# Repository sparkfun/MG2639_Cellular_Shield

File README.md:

**Note:Retired Product**
This product has been retired from our catalog and is no longer for sale. This page is made available for those looking for datasheets and the simply curious.

SparkFun MG2639 Cellular Shield
=========================

[*SparkFun MG2639 Cellular Shield (CEL-13120)*](https://www.sparkfun.com/products/13120)

The SparkFun MG2639 Cellular shield is an Arduino compatible shield that gives the user access to the MG2639_V3 GSM+GPS module. The module is capable of accquiring a GPS location as well as communication with GSM networks all over the world. Phonecalls can be made, texts sent, and data pushed to and read from web pages. All the supporting circuitry is provided including translation from 2.8V of the module to a user selectable 3.3V or 5V.

The main interface is two software serial ports.

Power can be provided either from the Arduino board's VIN or from an external battery such as a lithium polymer.

Repository Contents
-------------------

* **/Firmware** - Example sketches that work without the Arduino library.
* **/Hardware** - Schematic and PCB layout for the shield. Also includes an eagle library containing the various custom footprints for this shield. Specifically the MG2639 footprint.
* **/Documentation** - The AT command set, hardware guide, and various other datasheets.
* **/Libraries** - The SparkFun MG2639 Cellular Shield library.
* **/Production** - Production panel files.
* **[Hookup Guide](https://learn.sparkfun.com/tutorials/retired---mg2639-cellular-shield-hookup-guide)** - To get started using the MG2639 Cellular Shield, check out our tutorial!

License Information
-------------------
The hardware is released under [CERN Open Hardware License 1.2](http://www.ohwr.org/attachments/2388/cern_ohl_v_1_2.txt).
The code is beerware; if you see me (or any other SparkFun employee) at the local, and you've found our code helpful, please buy us a round!

Distributed as-is; no warranty is given.

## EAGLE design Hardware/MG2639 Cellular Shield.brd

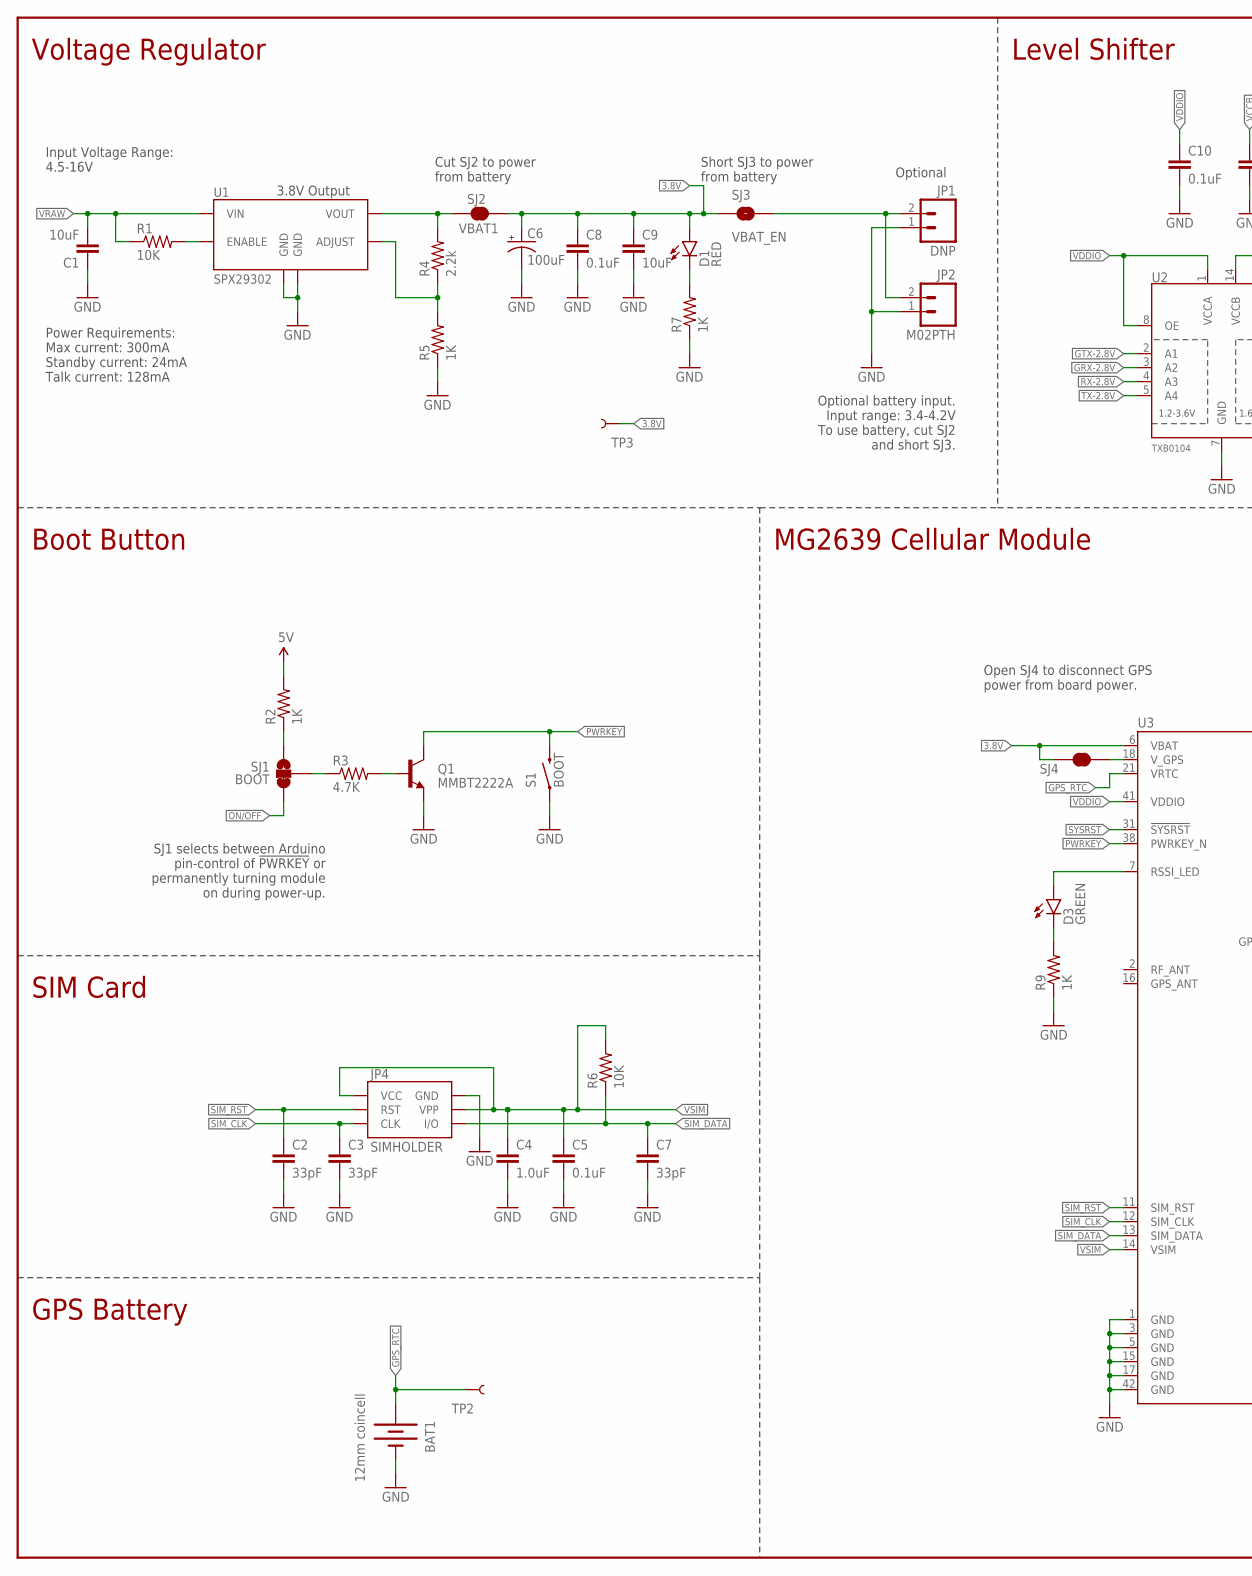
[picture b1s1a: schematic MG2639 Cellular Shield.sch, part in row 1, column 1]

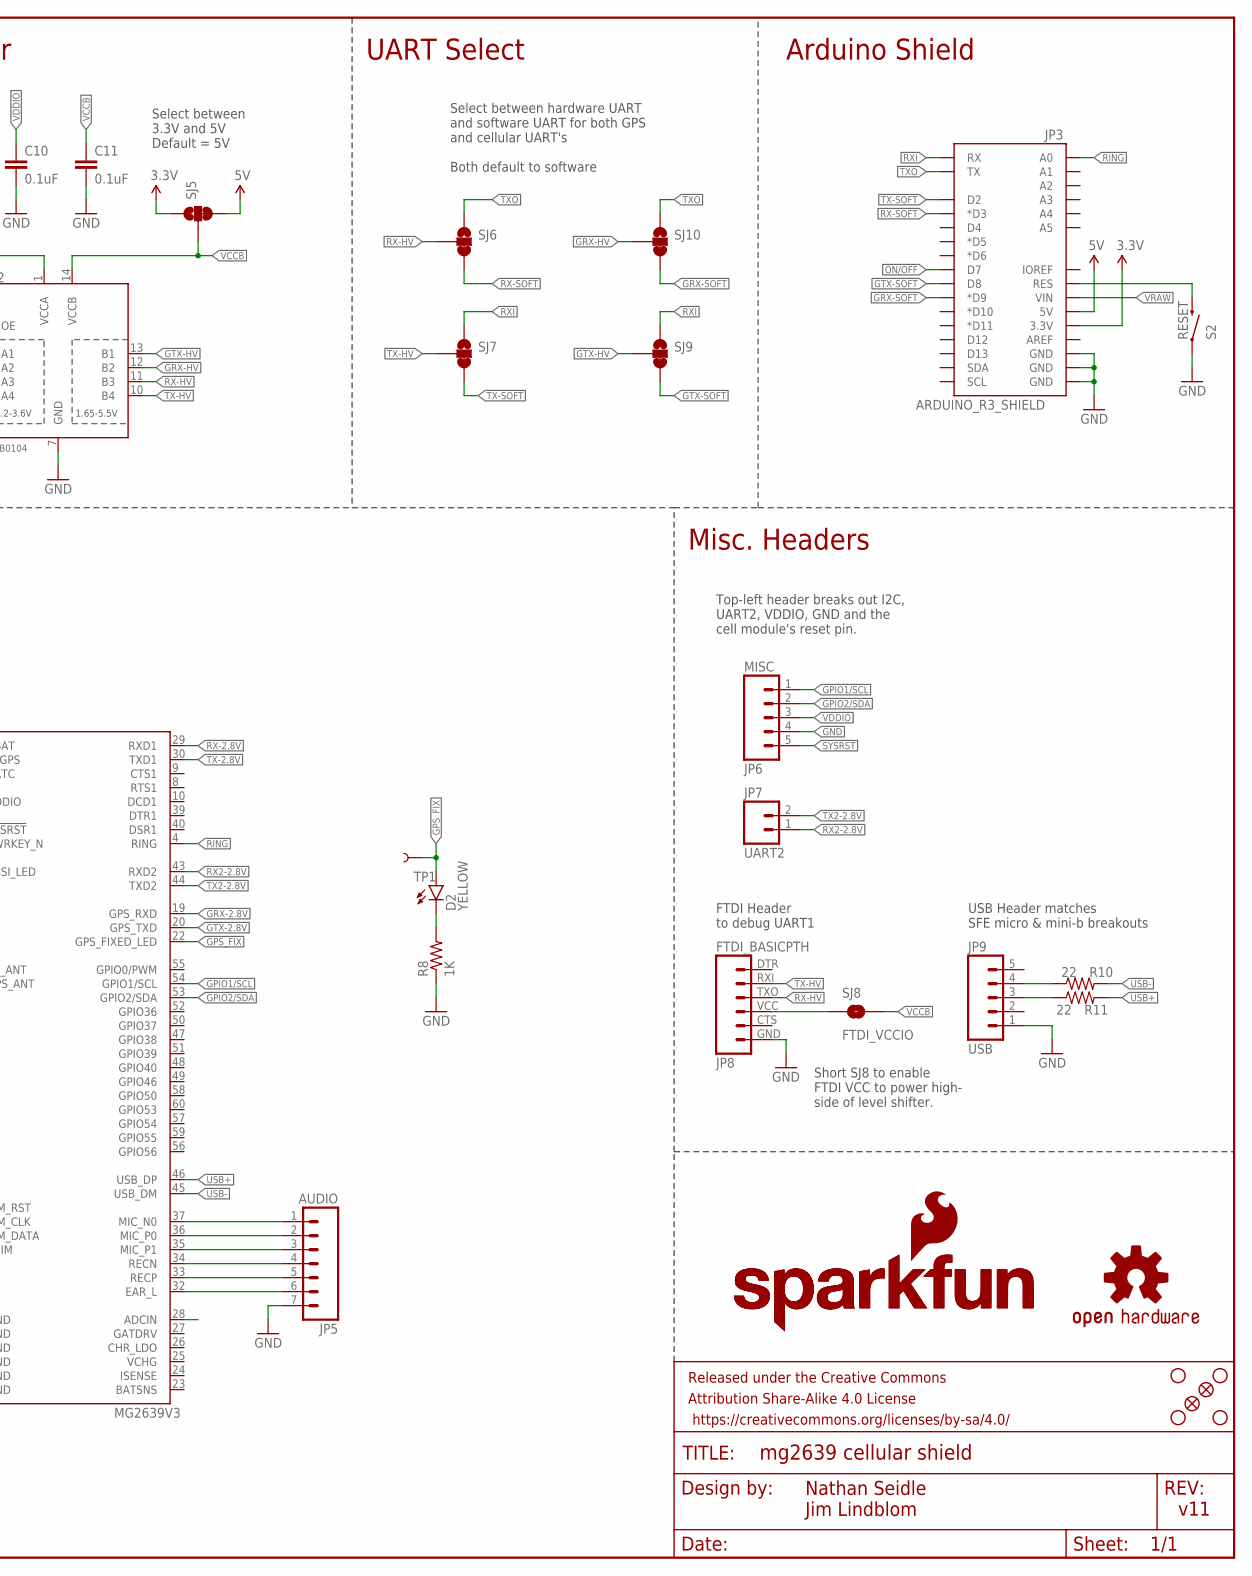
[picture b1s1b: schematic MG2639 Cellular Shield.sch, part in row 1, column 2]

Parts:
BAT1: 12mm coincell; BATTCON_12MM
C1, C9: 10uF; 1210
C2, C3, C7: 33pF; 0603-CAP
C4: 1.0uF; 0603-CAP
C5, C8, C10, C11: 0.1uF; 0603-CAP
C6: 100uF; EIA7343
D1: RED; LED-1206
D2: YELLOW; LED-1206
D3: GREEN; LED-1206
FID1, FID2: FIDUCIAL1X2; FIDUCIAL-1X2
FRAME1: FRAME-LEDGER; CREATIVE_COMMONS
JP1: DNP; JST-2-PTH
JP2: M02PTH; 1X02
JP3: ARDUINO_R3_SHIELD; UNO_R3_SHIELD_NOLABELS
JP4: SIMHOLDER
JP5: AUDIO; 1X07
JP6: MISC; 1X05
JP7: UART2; 1X02
JP8: FTDI_BASICPTH; FTDI_BASIC
JP9: USB; 1X05
LOGO1: SFE_LOGO_NAME.1_INCH; SFE_LOGO_NAME_.1
LOGO2: SFE_LOGO_NAME_FLAME.2_INCH; SFE_LOGO_NAME_FLAME_.2
LOGO3: OSHW-LOGOS; OSHW-LOGO-S
Q1: MMBT2222A; SOT23-3
R1, R6: 10K; 0603-RES
R2, R5, R7, R8, R9: 1K; 0603-RES
R3: 4.7K; 0603
R4: 2.2k; 0603-RES
R10, R11: 22; 0603-RES
S1: BOOT; TACTILE-SWITCH-SMD
S2: RESET; TACTILE-SWITCH-SMD
SJ1: BOOT; PAD-JUMPER-3-2OF3_NC_BY_TRACE_YES_SILK_FULL_BOX
SJ2: VBAT1; PAD-JUMPER-2-NC_BY_TRACE_YES_SILK
SJ3: VBAT_EN; PAD-JUMPER-2-NO_YES_SILK
SJ4: JUMPER-PAD-2-NC_BY_TRACE; PAD-JUMPER-2-NC_BY_TRACE_YES_SILK
SJ5, SJ6, SJ7, SJ9, SJ10: JUMPER-PAD-3-2OF3_NC_BY_TRACE; PAD-JUMPER-3-2OF3_NC_BY_TRACE_YES_SILK_FULL_BOX
SJ8: FTDI_VCCIO; PAD-JUMPER-2-NO_YES_SILK
STANDOFF1, STANDOFF2, STANDOFF3, STANDOFF4: STAND-OFF
TP1, TP2, TP3: TEST-POINT3X5; PAD.03X.05
U1: SPX29302; Q5-DD_SPX29300
U2: TXB0104; SO14
U3: MG2639V3; MG2639

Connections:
3.3V: JP3.3.3V, SJ5.1
3.8V: C6.A (+), C8.1, C9.1, D1.A, SJ2.2, SJ3.1, SJ4.1, TP3.P$1, U3.6 (VBAT)
5V: JP3.5V, R2.2, SJ5.3
!PWRKEY: Q1.3 (C), S1.3 (2), U3.38 (PWRKEY_N)
!SYSRST: JP6.5, U3.31 (!SYSRST)
ADCIN: U3.28 (ADCIN)
ADJUST: R4.1, R5.2, U1.5 (ADJUST)
EAR_L: JP5.6, U3.32 (EAR_L)
GND: BAT1.GND (-), C1.1, C2.2, C3.2, C4.2, C5.2, C6.C (-), C7.2, C8.2, C9.2, C10.2, C11.2, JP1.1, JP2.1, JP3.GND@0 (GND), JP3.GND@1 (GND), JP3.GND@2 (GND), JP4.C5 (GND), JP5.7, JP6.4, JP8.GND (6), JP9.1, Q1.2 (E), R5.1, R7.1, R8.1, R9.1, S1.1, S2.1, U1.3 (GND), U1.6 (GND), U2.7 (GND), U3.1 (GND), U3.3 (GND), U3.5 (GND), U3.15 (GND), U3.17 (GND), U3.42 (GND)
GPIO1/SCL: JP6.1, U3.54 (GPIO1/SCL)
GPIO2/SDA: JP6.2, U3.53 (GPIO2/SDA)
GPS_FIX: D2.A, TP1.P$1, U3.22 (GPS_FIXED_LED)
GPS_RTC: BAT1.PWR@1 (+), TP2.P$1, U3.21 (VRTC)
GRX-2.8V: U2.3 (A2), U3.19 (GPS_RXD)
GRX-HV: SJ10.2, U2.12 (B2)
GRX-SOFT: JP3.D9 (*D9), SJ10.3
GTX-2.8V: U2.2 (A1), U3.20 (GPS_TXD)
GTX-HV: SJ9.2, U2.13 (B1)
GTX-SOFT: JP3.D8, SJ9.3
MIC_N0: JP5.1, U3.37 (MIC_N0)
MIC_P0: JP5.2, U3.36 (MIC_P0)
MIC_P1: JP5.3, U3.35 (MIC_P1)
unnamed: R1.2, U1.1 (ENABLE)
unnamed: JP9.4, R10.1
unnamed: Q1.1 (B), R3.2
unnamed: R4.2, SJ2.1, U1.4 (VOUT)
unnamed: R3.1, SJ1.2
unnamed: R2.1, SJ1.1
unnamed: D3.A, U3.7 (RSSI_LED)
unnamed: D3.C, R9.2
unnamed: D2.C, R8.2
unnamed: JP9.3, R11.1
unnamed: JP8.VCC (4), SJ8.1
unnamed: JP1.2, JP2.2, SJ3.2
unnamed: D1.C, R7.2
ON/OFF: JP3.D7, SJ1.3
RECN: JP5.4, U3.34 (RECN)
RECP: JP5.5, U3.33 (RECP)
RESET: JP3.RES, S2.3 (2)
RING: JP3.A0, U3.4 (RING)
RX2-2.8V: JP7.1, U3.43 (RXD2)
RX-2.8V: U2.4 (A3), U3.29 (RXD1)
RX-HV: JP8.TXO (3), SJ6.2, U2.11 (B3)
RX-SOFT: JP3.D3 (*D3), SJ6.3
RXI: JP3.RX, SJ7.1, SJ9.1
SIM_CLK: C3.1, JP4.C3 (CLK), U3.12 (SIM_CLK)
SIM_DATA: C7.1, JP4.C7 (I/O), R6.1, U3.13 (SIM_DATA)
SIM_RST: C2.1, JP4.C2 (RST), U3.11 (SIM_RST)
TX2-2.8V: JP7.2, U3.44 (TXD2)
TX-2.8V: U2.5 (A4), U3.30 (TXD1)
TX-HV: JP8.RXI (2), SJ7.2, U2.10 (B4)
TX-SOFT: JP3.D2, SJ7.3
TXO: JP3.TX, SJ6.1, SJ10.1
USB+: R11.2, U3.46 (USB_DP)
USB-: R10.2, U3.45 (USB_DM)
VCCB: C11.1, SJ5.2, SJ8.2, U2.14 (VCCB)
VCHG: U3.25 (VCHG)
VDDIO: C10.1, JP6.3, U2.1 (VCCA), U2.8 (OE), U3.41 (VDDIO)
VRAW: C1.2, JP3.VIN, R1.1, U1.2 (VIN)
VSIM: C4.1, C5.1, JP4.C1 (VCC), JP4.C6 (VPP), R6.2, U3.14 (VSIM)
V_GPS: SJ4.2, U3.18 (V_GPS)

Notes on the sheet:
3.8V Output
Select between 3.3V and 5V Default = 5V
Select between hardware UART and software UART for both GPS and cellular UART's Both default to software
Cut SJ2 to power from battery
Optional
Nathan Seidle Jim Lindblom
Open SJ4 to disconnect GPS power from board power.
v11
Voltage Regulator
Level Shifter
UART Select
Arduino Shield
Misc. Headers
MG2639 Cellular Module
Boot Button
SIM Card
GPS Battery
FTDI Header to debug UART1
USB Header matches SFE micro & mini-b breakouts
Top-left header breaks out I2C, UART2, VDDIO, GND and the cell module's reset pin.
Short SJ3 to power from battery
Optional battery input. Input range: 3.4-4.2V To use battery, cut SJ2 and short SJ3.
Input Voltage Range: 4.5-16V
Power Requirements: Max current: 300mA Standby current: 24mA Talk current: 128mA
Short SJ8 to enable FTDI VCC to power high- side of level shifter.
SJ1 selects between Arduino pin-control of !PWRKEY! or permanently turning module on during power-up.

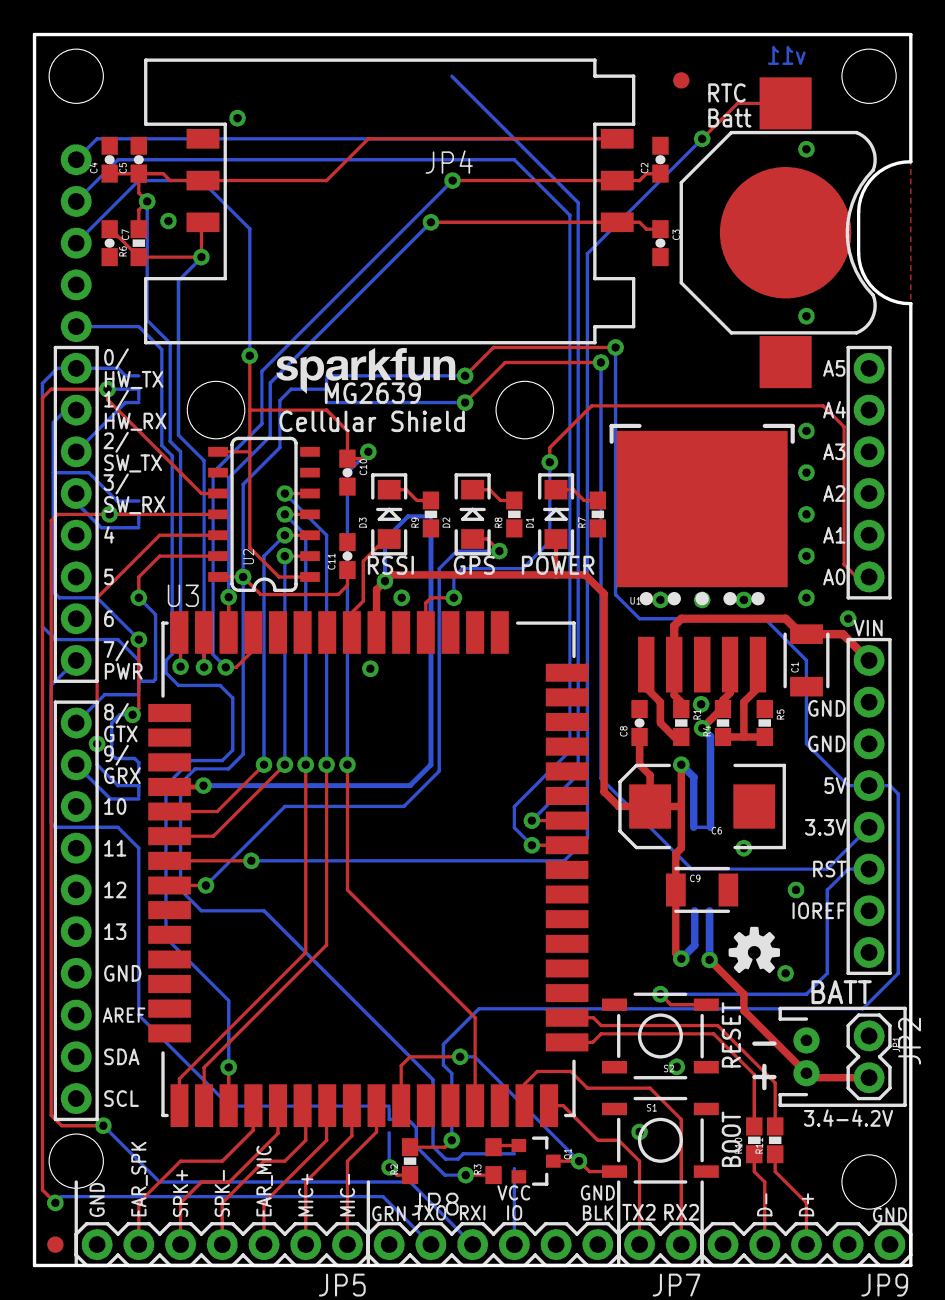
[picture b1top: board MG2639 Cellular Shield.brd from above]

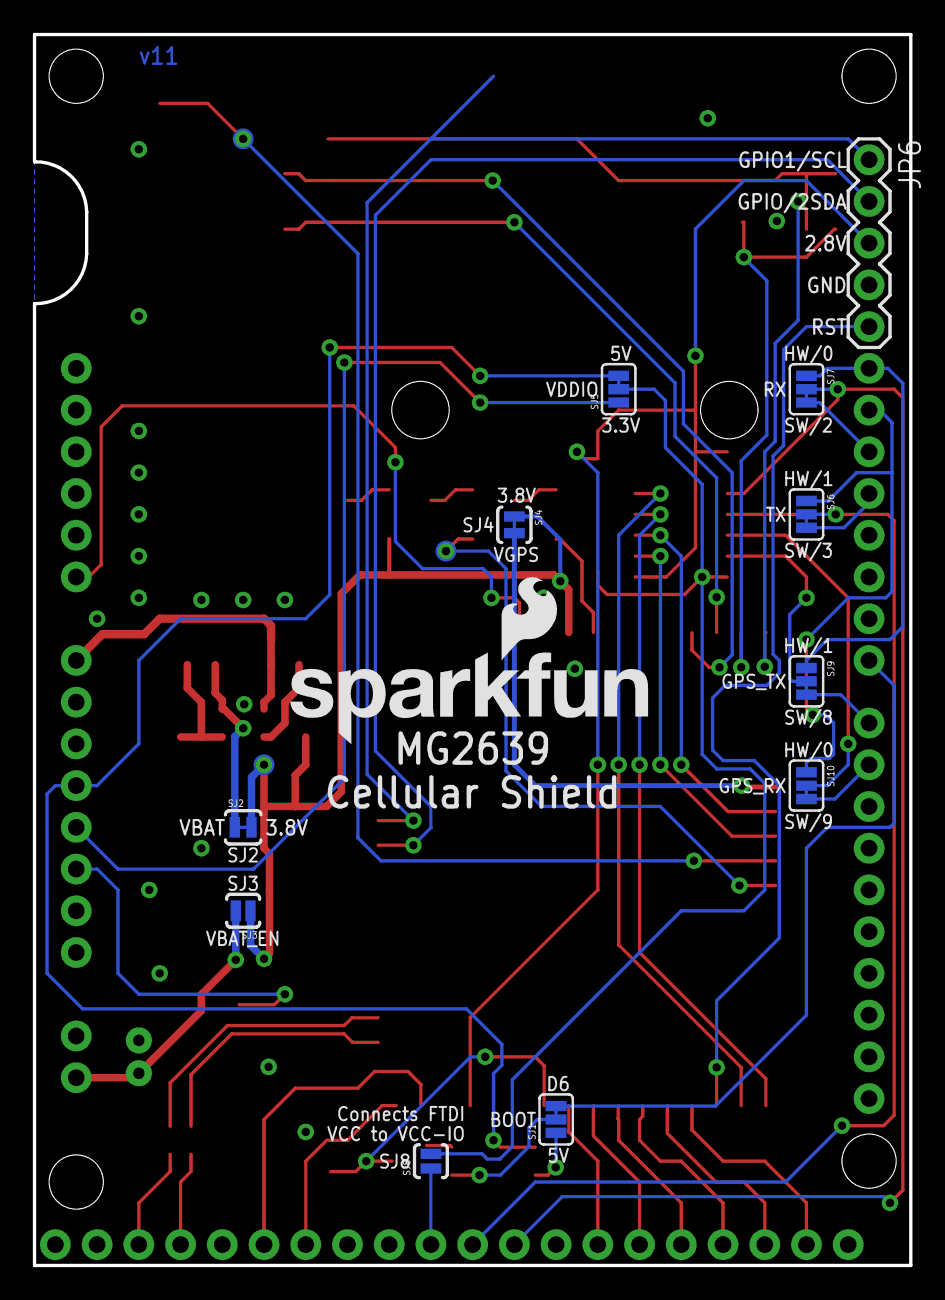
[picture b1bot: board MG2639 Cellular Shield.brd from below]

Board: 2 copper layers, 53.3 x 74.9 mm, 64 parts (15 on the bottom side), 59 nets.

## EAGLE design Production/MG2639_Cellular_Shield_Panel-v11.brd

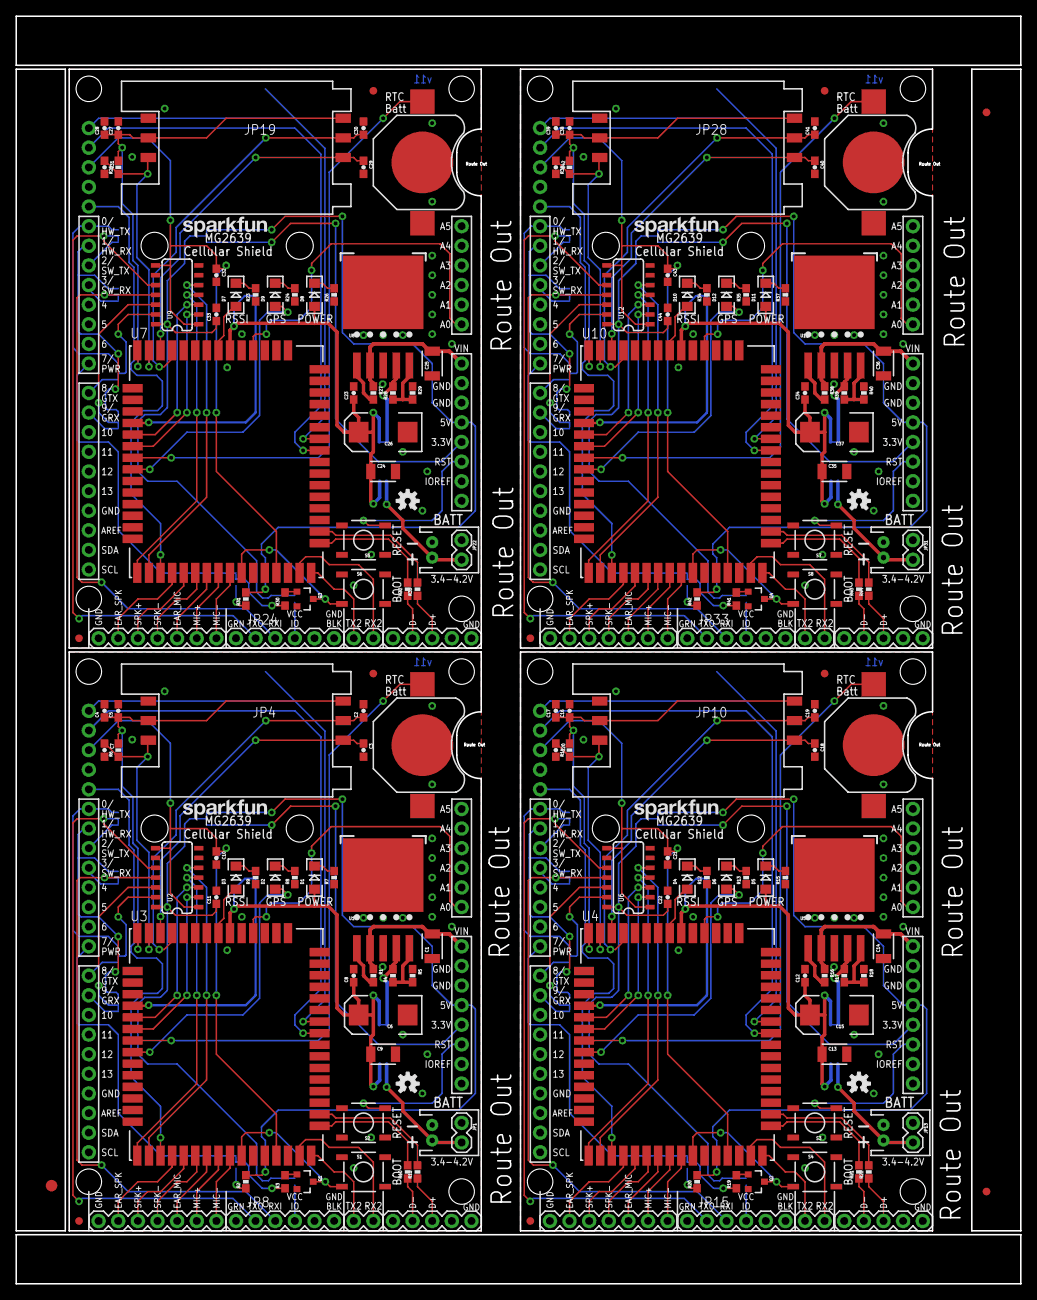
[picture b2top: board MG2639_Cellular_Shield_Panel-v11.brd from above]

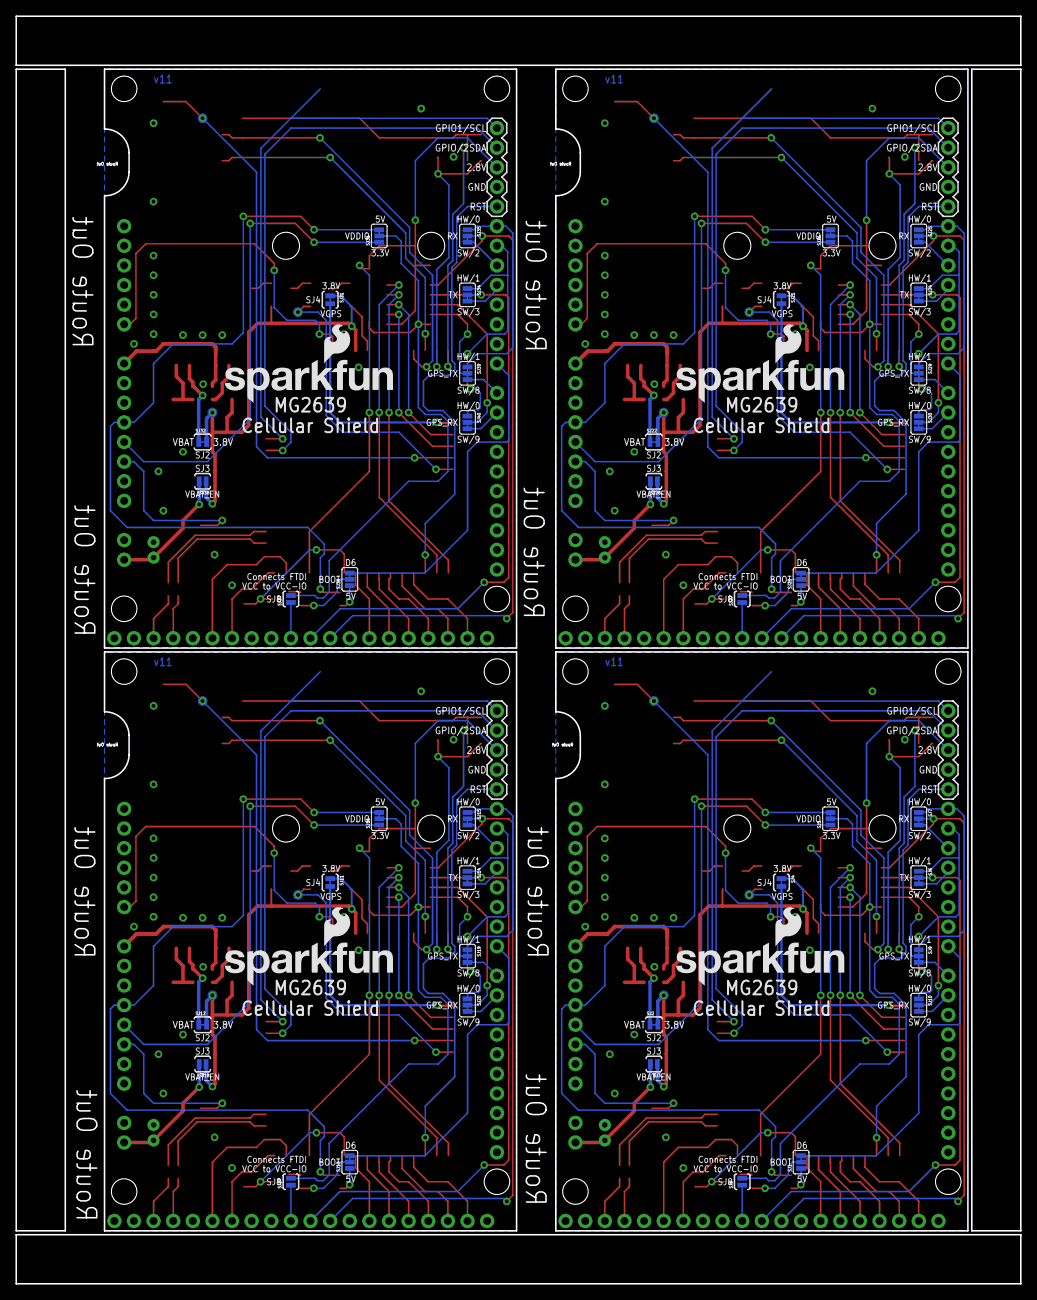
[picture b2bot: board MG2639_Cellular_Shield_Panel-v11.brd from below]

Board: 2 copper layers, 130.0 x 164.1 mm, 255 parts (60 on the bottom side), 236 nets.

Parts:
BAT1, BAT2, BAT3, BAT4: 12mm coincell; BATTCON_12MM
C1, C9, C13, C14, C24, C25, C35, C36: 10uF; 1210
C2, C3, C7, C18, C19, C20, C29, C30, C31, C40, C41, C42: 33pF; 0603-CAP
C4, C17, C28, C39: 1.0uF; 0603-CAP
C5, C8, C10, C11, C12, C16, C21, C22, C23, C27, C32, C33, C34, C38, C43, C44: 0.1uF; 0603-CAP
C6, C15, C26, C37: 100uF; EIA7343
D1, D5, D8, D11: RED; LED-1206
D2, D6, D9, D12: YELLOW; LED-1206
D3, D4, D7, D10: GREEN; LED-1206
E$1: FIDUCIAL-1.5X3
E$4, E$5: FIDUCIAL-1X2
FID1, FID2, FID3, FID4, FID5, FID6, FID7, FID8: FIDUCIAL1X2; FIDUCIAL-1X2
JP1, JP13, JP22, JP31: LiPo; JST-2-PTH
JP2, JP16, JP25, JP34: M02PTH; 1X02
JP3, JP11, JP20, JP29: ARDUINO_R3_SHIELD; UNO_R3_SHIELD_NOLABELS
JP4, JP10, JP19, JP28: SIMHOLDER
JP5, JP12, JP21, JP30: AUDIO; 1X07
JP6, JP18, JP27, JP36: MISC; 1X05
JP7, JP17, JP26, JP35: UART2; 1X02
JP8, JP15, JP24, JP33: FTDI_BASICPTH; FTDI_BASIC
JP9, JP14, JP23, JP32: USB; 1X05
LOGO1, LOGO6, LOGO9, LOGO12: SFE_LOGO_NAME.1_INCH; SFE_LOGO_NAME_.1
LOGO2, LOGO5, LOGO8, LOGO11: SFE_LOGO_NAME_FLAME.2_INCH; SFE_LOGO_NAME_FLAME_.2
LOGO3, LOGO4, LOGO7, LOGO10: OSHW-LOGOS; OSHW-LOGO-S
Q1, Q2, Q3, Q4: MMBT2222A; SOT23-3
R1, R6, R14, R16, R25, R27, R36, R38: 10K; 0603-RES
R2, R5, R7, R8, R9, R12, R13, R15, R18, R20, R23, R24, R26, R29, R31, R34, R35, R37, R40, R42: 1K; 0603-RES
R3, R19, R30, R41: 4.7K; 0603
R4, R17, R28, R39: 2.2k; 0603-RES
R10, R11, R21, R22, R32, R33, R43, R44: 22; 0603-RES
S1, S4, S6, S8: BOOT; TACTILE-SWITCH-SMD
S2, S3, S5, S7: RESET; TACTILE-SWITCH-SMD
SJ1, SJ13, SJ23, SJ33: BOOT; PAD-JUMPER-3-2OF3_NC_BY_TRACE_YES_SILK_FULL_BOX
SJ2, SJ12, SJ22, SJ32: VBAT1; PAD-JUMPER-2-NC_BY_TRACE_YES_SILK
SJ3, SJ18, SJ28, SJ38: VBAT_EN; PAD-JUMPER-2-NO_YES_SILK
SJ4, SJ11, SJ21, SJ31: PAD-JUMPER-2-NC_BY_TRACE_YES_SILK
SJ5, SJ6, SJ7, SJ9, SJ10, SJ14, SJ15, SJ16, SJ19, SJ20, SJ24, SJ25, SJ26, SJ29, SJ30, SJ34, SJ35, SJ36, SJ39, SJ40: PAD-JUMPER-3-2OF3_NC_BY_TRACE_YES_SILK_FULL_BOX
SJ8, SJ17, SJ27, SJ37: FTDI_VCCIO; PAD-JUMPER-2-NO_YES_SILK
STANDOFF1, STANDOFF2, STANDOFF3, STANDOFF4, STANDOFF5, STANDOFF6, STANDOFF7, STANDOFF8, STANDOFF9, STANDOFF10, STANDOFF11, STANDOFF12, STANDOFF13, STANDOFF14, STANDOFF15, STANDOFF16: STAND-OFF
TP1, TP2, TP3, TP4, TP5, TP6, TP7, TP8, TP9, TP10, TP11, TP12: PAD.03X.05
U1, U5, U8, U11: SPX29302; Q5-DD_SPX29300
U2, U6, U9, U12: TXB0104; SO14
U3, U4, U7, U10: MG2639V3; MG2639

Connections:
3.3V: JP3.3.3V, SJ5.1
3.3V1: JP11.3.3V, SJ16.1
3.3V2: JP20.3.3V, SJ26.1
3.3V3: JP29.3.3V, SJ36.1
3.8V: C6.A, C8.1, C9.1, D1.A, SJ2.2, SJ3.1, SJ4.1, TP3.P$1, U3.6
3.8V1: C12.1, C13.1, C15.A, D5.A, SJ11.1, SJ12.2, SJ18.1, TP6.P$1, U4.6
3.8V2: C23.1, C24.1, C26.A, D8.A, SJ21.1, SJ22.2, SJ28.1, TP9.P$1, U7.6
3.8V3: C34.1, C35.1, C37.A, D11.A, SJ31.1, SJ32.2, SJ38.1, TP12.P$1, U10.6
5V: JP3.5V, R2.2, SJ5.3
5V1: JP11.5V, R20.2, SJ16.3
5V2: JP20.5V, R31.2, SJ26.3
5V3: JP29.5V, R42.2, SJ36.3
!PWRKEY: Q1.3, S1.3, U3.38
!PWRKEY1: Q2.3, S4.3, U4.38
!PWRKEY2: Q3.3, S6.3, U7.38
!PWRKEY3: Q4.3, S8.3, U10.38
!SYSRST: JP6.5, U3.31
!SYSRST1: JP18.5, U4.31
!SYSRST2: JP27.5, U7.31
!SYSRST3: JP36.5, U10.31
ADJUST: R4.1, R5.2, U1.5
ADJUST1: R17.1, R18.2, U5.5
ADJUST2: R28.1, R29.2, U8.5
ADJUST3: R39.1, R40.2, U11.5
EAR_L: JP5.6, U3.32
EAR_L1: JP12.6, U4.32
EAR_L2: JP21.6, U7.32
EAR_L3: JP30.6, U10.32
GND: BAT1.GND, C1.1, C2.2, C3.2, C4.2, C5.2, C6.C, C7.2, C8.2, C9.2, C10.2, C11.2, JP1.1, JP2.1, JP3.GND@0, JP3.GND@1, JP3.GND@2, JP4.C5, JP5.7, JP6.4, JP8.GND, JP9.1, Q1.2, R5.1, R7.1, R8.1, R9.1, S1.1, S2.1, U1.3, U1.6, U2.7, U3.1, U3.3, U3.5, U3.15, U3.17, U3.42
GND1: BAT2.GND, C12.2, C13.2, C14.1, C15.C, C16.2, C17.2, C18.2, C19.2, C20.2, C21.2, C22.2, JP10.C5, JP11.GND@0, JP11.GND@1, JP11.GND@2, JP12.7, JP13.1, JP14.1, JP15.GND, JP16.1, JP18.4, Q2.2, R12.1, R13.1, R15.1, R18.1, S3.1, S4.1, U4.1, U4.3, U4.5, U4.15, U4.17, U4.42, U5.3, U5.6, U6.7
GND2: BAT3.GND, C23.2, C24.2, C25.1, C26.C, C27.2, C28.2, C29.2, C30.2, C31.2, C32.2, C33.2, JP19.C5, JP20.GND@0, JP20.GND@1, JP20.GND@2, JP21.7, JP22.1, JP23.1, JP24.GND, JP25.1, JP27.4, Q3.2, R23.1, R24.1, R26.1, R29.1, S5.1, S6.1, U7.1, U7.3, U7.5, U7.15, U7.17, U7.42, U8.3, U8.6, U9.7
GND3: BAT4.GND, C34.2, C35.2, C36.1, C37.C, C38.2, C39.2, C40.2, C41.2, C42.2, C43.2, C44.2, JP28.C5, JP29.GND@0, JP29.GND@1, JP29.GND@2, JP30.7, JP31.1, JP32.1, JP33.GND, JP34.1, JP36.4, Q4.2, R34.1, R35.1, R37.1, R40.1, S7.1, S8.1, U10.1, U10.3, U10.5, U10.15, U10.17, U10.42, U11.3, U11.6, U12.7
GPIO1/SCL: JP6.1, U3.54
GPIO1/SCL1: JP18.1, U4.54
GPIO1/SCL2: JP27.1, U7.54
GPIO1/SCL3: JP36.1, U10.54
GPIO2/SDA: JP6.2, U3.53
GPIO2/SDA1: JP18.2, U4.53
GPIO2/SDA2: JP27.2, U7.53
GPIO2/SDA3: JP36.2, U10.53
GPS_FIX: D2.A, TP1.P$1, U3.22
GPS_FIX1: D6.A, TP4.P$1, U4.22
GPS_FIX2: D9.A, TP7.P$1, U7.22
GPS_FIX3: D12.A, TP10.P$1, U10.22
GPS_RTC: BAT1.PWR@1, TP2.P$1, U3.21
GPS_RTC1: BAT2.PWR@1, TP5.P$1, U4.21
GPS_RTC2: BAT3.PWR@1, TP8.P$1, U7.21
GPS_RTC3: BAT4.PWR@1, TP11.P$1, U10.21
GRX-2.8V: U2.3, U3.19
GRX-2.8V1: U4.19, U6.3
GRX-2.8V2: U7.19, U9.3
GRX-2.8V3: U10.19, U12.3
GRX-HV: SJ10.2, U2.12
GRX-HV1: SJ20.2, U6.12
GRX-HV2: SJ30.2, U9.12
GRX-HV3: SJ40.2, U12.12
GRX-SOFT: JP3.D9, SJ10.3
GRX-SOFT1: JP11.D9, SJ20.3
GRX-SOFT2: JP20.D9, SJ30.3
GRX-SOFT3: JP29.D9, SJ40.3
GTX-2.8V: U2.2, U3.20
GTX-2.8V1: U4.20, U6.2
GTX-2.8V2: U7.20, U9.2
GTX-2.8V3: U10.20, U12.2
GTX-HV: SJ9.2, U2.13
GTX-HV1: SJ19.2, U6.13
GTX-HV2: SJ29.2, U9.13
GTX-HV3: SJ39.2, U12.13
GTX-SOFT: JP3.D8, SJ9.3
GTX-SOFT1: JP11.D8, SJ19.3
GTX-SOFT2: JP20.D8, SJ29.3
GTX-SOFT3: JP29.D8, SJ39.3
MIC_N0: JP5.1, U3.37
MIC_N1: JP12.1, U4.37
MIC_N2: JP21.1, U7.37
MIC_N3: JP30.1, U10.37
MIC_P0: JP5.2, U3.36
MIC_P1: JP5.3, U3.35
MIC_P2: JP12.3, U4.35
MIC_P3: JP12.2, U4.36
MIC_P4: JP21.3, U7.35
MIC_P5: JP21.2, U7.36
MIC_P6: JP30.3, U10.35
MIC_P7: JP30.2, U10.36
unnamed: R1.2, U1.1
unnamed: JP9.4, R10.1
unnamed: Q1.1, R3.2
unnamed: R4.2, SJ2.1, U1.4
unnamed: R3.1, SJ1.2
unnamed: R2.1, SJ1.1
unnamed: D3.A, U3.7
unnamed: D3.C, R9.2
unnamed: D2.C, R8.2
unnamed: JP9.3, R11.1
unnamed: JP8.VCC, SJ8.1
unnamed: JP1.2, JP2.2, SJ3.2
unnamed: D5.C, R15.2
unnamed: R16.2, U5.1
unnamed: Q2.1, R19.2
unnamed: R19.1, SJ13.2
unnamed: D1.C, R7.2
unnamed: D4.A, U4.7
unnamed: D4.C, R12.2
unnamed: D6.C, R13.2
unnamed: R17.2, SJ12.1, U5.4
unnamed: R20.1, SJ13.1
unnamed: JP14.4, R21.1
unnamed: JP14.3, R22.1
unnamed: JP15.VCC, SJ17.1
unnamed: JP13.2, JP16.2, SJ18.2
unnamed: D8.C, R26.2
unnamed: R27.2, U8.1
unnamed: Q3.1, R30.2
unnamed: R30.1, SJ23.2
unnamed: D7.A, U7.7
unnamed: D7.C, R23.2
unnamed: D9.C, R24.2
unnamed: R28.2, SJ22.1, U8.4
unnamed: R31.1, SJ23.1
unnamed: JP23.4, R32.1
unnamed: JP23.3, R33.1
unnamed: JP24.VCC, SJ27.1
unnamed: JP22.2, JP25.2, SJ28.2
unnamed: D11.C, R37.2
unnamed: R38.2, U11.1
unnamed: Q4.1, R41.2
unnamed: R41.1, SJ33.2
unnamed: D10.A, U10.7
unnamed: D10.C, R34.2
unnamed: D12.C, R35.2
unnamed: R39.2, SJ32.1, U11.4
unnamed: R42.1, SJ33.1
unnamed: JP32.4, R43.1
unnamed: JP32.3, R44.1
unnamed: JP33.VCC, SJ37.1
unnamed: JP31.2, JP34.2, SJ38.2
ON/OFF: JP3.D7, SJ1.3
ON/OFF1: JP11.D7, SJ13.3
ON/OFF2: JP20.D7, SJ23.3
ON/OFF3: JP29.D7, SJ33.3
RECN: JP5.4, U3.34
RECN1: JP12.4, U4.34
RECN2: JP21.4, U7.34
RECN3: JP30.4, U10.34
RECP: JP5.5, U3.33
RECP1: JP12.5, U4.33
RECP2: JP21.5, U7.33
RECP3: JP30.5, U10.33
RESET: JP3.RES, S2.3
RESET1: JP11.RES, S3.3
RESET2: JP20.RES, S5.3
RESET3: JP29.RES, S7.3
RING: JP3.A0, U3.4
RING1: JP11.A0, U4.4
RING2: JP20.A0, U7.4
RING3: JP29.A0, U10.4
RX2-2.8V: JP7.1, U3.43
RX2-2.8V1: JP17.1, U4.43
RX2-2.8V2: JP26.1, U7.43
RX2-2.8V3: JP35.1, U10.43
RX-2.8V: U2.4, U3.29
RX-2.8V1: U4.29, U6.4
RX-2.8V2: U7.29, U9.4
RX-2.8V3: U10.29, U12.4
RX-HV: JP8.TXO, SJ6.2, U2.11
RX-HV1: JP15.TXO, SJ14.2, U6.11
RX-HV2: JP24.TXO, SJ24.2, U9.11
RX-HV3: JP33.TXO, SJ34.2, U12.11
RX-SOFT: JP3.D3, SJ6.3
RX-SOFT1: JP11.D3, SJ14.3
RX-SOFT2: JP20.D3, SJ24.3
RX-SOFT3: JP29.D3, SJ34.3
RXI: JP3.RX, SJ7.1, SJ9.1
RXI1: JP11.RX, SJ15.1, SJ19.1
RXI2: JP20.RX, SJ25.1, SJ29.1
RXI3: JP29.RX, SJ35.1, SJ39.1
SIM_CLK: C3.1, JP4.C3, U3.12
SIM_CLK1: C18.1, JP10.C3, U4.12
SIM_CLK2: C29.1, JP19.C3, U7.12
SIM_CLK3: C40.1, JP28.C3, U10.12
SIM_DATA: C7.1, JP4.C7, R6.1, U3.13
SIM_DATA1: C20.1, JP10.C7, R14.1, U4.13
SIM_DATA2: C31.1, JP19.C7, R25.1, U7.13
SIM_DATA3: C42.1, JP28.C7, R36.1, U10.13
SIM_RST: C2.1, JP4.C2, U3.11
SIM_RST1: C19.1, JP10.C2, U4.11
SIM_RST2: C30.1, JP19.C2, U7.11
SIM_RST3: C41.1, JP28.C2, U10.11
TX2-2.8V: JP7.2, U3.44
TX2-2.8V1: JP17.2, U4.44
TX2-2.8V2: JP26.2, U7.44
TX2-2.8V3: JP35.2, U10.44
TX-2.8V: U2.5, U3.30
TX-2.8V1: U4.30, U6.5
TX-2.8V2: U7.30, U9.5
TX-2.8V3: U10.30, U12.5
TX-HV: JP8.RXI, SJ7.2, U2.10
TX-HV1: JP15.RXI, SJ15.2, U6.10
TX-HV2: JP24.RXI, SJ25.2, U9.10
TX-HV3: JP33.RXI, SJ35.2, U12.10
TX-SOFT: JP3.D2, SJ7.3
TX-SOFT1: JP11.D2, SJ15.3
TX-SOFT2: JP20.D2, SJ25.3
TX-SOFT3: JP29.D2, SJ35.3
TXO: JP3.TX, SJ6.1, SJ10.1
TXO1: JP11.TX, SJ14.1, SJ20.1
TXO2: JP20.TX, SJ24.1, SJ30.1
TXO3: JP29.TX, SJ34.1, SJ40.1
USB+: R11.2, U3.46
USB+1: R22.2, U4.46
USB+2: R33.2, U7.46
USB+3: R44.2, U10.46
USB-: R10.2, U3.45
USB-1: R21.2, U4.45
USB-2: R32.2, U7.45
USB-3: R43.2, U10.45
VCCB: C11.1, SJ5.2, SJ8.2, U2.14
VCCB1: C22.1, SJ16.2, SJ17.2, U6.14
VCCB2: C33.1, SJ26.2, SJ27.2, U9.14
VCCB3: C44.1, SJ36.2, SJ37.2, U12.14
VDDIO: C10.1, JP6.3, U2.1, U2.8, U3.41
VDDIO1: C21.1, JP18.3, U4.41, U6.1, U6.8
VDDIO2: C32.1, JP27.3, U7.41, U9.1, U9.8
VDDIO3: C43.1, JP36.3, U10.41, U12.1, U12.8
VRAW: C1.2, JP3.VIN, R1.1, U1.2
VRAW1: C14.2, JP11.VIN, R16.1, U5.2
VRAW2: C25.2, JP20.VIN, R27.1, U8.2
VRAW3: C36.2, JP29.VIN, R38.1, U11.2
VSIM: C4.1, C5.1, JP4.C1, JP4.C6, R6.2, U3.14
VSIM1: C16.1, C17.1, JP10.C1, JP10.C6, R14.2, U4.14
VSIM2: C27.1, C28.1, JP19.C1, JP19.C6, R25.2, U7.14
VSIM3: C38.1, C39.1, JP28.C1, JP28.C6, R36.2, U10.14
V_GPS: SJ4.2, U3.18
V_GPS1: SJ11.2, U4.18
V_GPS2: SJ21.2, U7.18
V_GPS3: SJ31.2, U10.18

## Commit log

2014-09-16 :neckbeard: Added .gitattributes & .gitignore files
2014-09-17 Corrected +/- on battery connector
2014-10-05 Prelim firmware. Works for certain features.
2014-10-06 Update ignore and readme.
2014-10-06 Updating readme with images
2014-10-06 Removing Eagle's backup files.
2014-10-06 Adding PDF of schematic
2014-10-20 Filling out info in header
    Removed mentions to the battery management IC
    Added info from schematic on Jumpers
    Added note on external power requirement
2014-10-20 Getting basic SMS and TCP working.
2014-10-20 Adding GSMSHIELD library
    This is a library for the SIM900 that has been tweaked to work with
    MG2639. It should compile but it's not really ironed out yet.
2014-10-31 Add silk labels to pins/jumpers. Add FTDI header. Remove SYSRST circuit. Reconfiguring jumpers. Removed USB connector, broke USB pins out to headers.
2014-10-31 adding pdf schematic of v10
2014-11-03 re-routing around TXB0108, cleaning up some silk.
2014-11-03 adding 22 ohm resistors to D+/D-. placing more vias around vreg.
2014-11-03 removing .l#n backup files, not sure why the didn't get gitignored.
2014-11-03 rearranging LEDs - moving GPS LED up with others.
2014-11-04 Switching TXB0108 to a TXB0104. Breaking out I2C pins, 2.8V. Fixing some silk.
2014-11-04 Updating Board Layout image
2014-11-04 updating PDF schematic to match current board file
2015-01-09 Routing UART1 to FTDI header instead of GPS. Adding TP's. Fixing silk. Routing out GPS battery pull-out area.
2015-01-13 Adding stand-off holes. Moving GPS UART to pins 8/9 (better support for faster buad rates). Adding jumpers to select hardware UART for GPS too.
2015-01-13 Defaulting TXB0104 HV to 5V. Fixing connector names. Adding measures.
2015-01-14 Adding production ID to MG2639 Cell module.
2015-01-15 Adding test point to 3.8V bus.
2015-01-15 Re-routing GTX-HV to D8 on the Arduino.
2015-01-15 Cleaning up nets around Arduino Shield connector (removing stubs).
2015-01-20 Switching GPS fix indicator LED to yellow.
2015-01-21 moved board fiducial
2015-01-21 created panel v11
2015-04-07 Updating schematic PDF. Moving Eagle library.
    - Deleted library folder to avoid confusion with incoming libraries folder
    (Arduino library).
    - Deleted MG2639 Cellular Shield.txt
2015-04-07 Initial commit of SparkFun MG2639 Arduino library
2015-04-07 Adding keywords.txt to library.
2015-04-07 Removing GSMShield library.
2015-04-07 Renaming directories to match template.
    Removing "Marked" datasheets.
2015-04-07 Updating README.md. Removing unlinked images.
2015-04-07 Updating README.md
2015-05-07 Removing Libraries folder - will be subtreed next.
2015-05-07 Squashed 'Libraries/Arduino/' content from commit 4f0d0cb
    git-subtree-dir: Libraries/Arduino
    git-subtree-split: 4f0d0cb55587b8f950655b3f631f1b648792c77b
2015-05-07 Adding readme to Libraries folder.
2016-03-29 Updating LiPo connector value to DNP
2018-03-29 Updated readme -retired status and correct guide link
    Updated readme to reflect retired status of this product and corrected the hookup guide link

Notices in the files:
parts and their libraries:
SparkFun-Capacitors: Licensing: Creative Commons ShareAlike 4.0 International - https://creativecommons.org/licenses/by-sa/4.0
SparkFun-Aesthetics: Released under the Creative Commons Attribution Share-Alike 4.0 License
SparkFun-Aesthetics: https://creativecommons.org/licenses/by-sa/4.0
